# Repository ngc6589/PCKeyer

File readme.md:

# PCKeyer
## 概要

PCKeyer はお手持ちのエレキーと無線機の KEY ジャック間に入れることで、PCキーイング機能を追加するためのアダプタ基板です。

CTESTWIN や DSCW (Didital Sound CW) などから、シリアルポートの RTS/DTR を使用したキーイングをすることが出来ます。

パドル -> エレキー -> 当アダプタ -> リグのキージャック という接続です。

## プリント基板について

基板は https://www.em9system.com/?p=956 にて頒布いたします。

## 部品表  

|部品名|秋月型番|数量|その他|
|-----|-----|----|----|
|FT232RL USBシリアル変換モジュールキット|K-06693|1||
|抵抗入トランジスタ DTA123EL|I-12465|1||
|フォトカプラ PC817|I-13765|1||
|丸ピンICソケット(4P)|P-14240|1||
|カーボン抵抗(炭素皮膜抵抗) 1/4W180Ω(100本入)|R-25181|1袋||
|3.5mmステレオミニジャック MJ-352W-O|C-08958|2||
|ジャンパーピン赤(2.54mmピッチ)(25個入)|P-03688|1袋||
|ピンヘッダ 1×40 (40P)|C-00167|1||
|＜以下オプション＞
|C基板用アクリルパネル(アクリル板) 2mm厚(透明)|P-09853|1|スモークは P-09854|
|3mmプラネジ(7mm)+六角スペーサー(14mm)セット|P-01861|1||
|接着シール付き透明ゴムクッション (4個入)|P-10080|1||

抵抗入トランジスタ DTA123EL は、他のデジトラに置き換え可能です。または2SA1015 などの汎用 PNP トランジスタと 2.2k 程度のベース抵抗の組み合わせでも OK です。足の並びは ECB です。  
フォトカプラは TLP521 など汎用品置き換え可能です。  

## 組み立て

- FT232RL USBシリアル変換モジュールキットは、 USB からの 5V で動作させたいのでジャンパーJ1 2-3間ショート、J2 ショートとします。
- 0「ゼロ」と書かれた抵抗部分は、抵抗入りトランジスタを使用する場合はショートです。2SA1015 など汎用 PNP トランジスタを使うときだけここにベース抵抗を取り付けます。

## 注意事項

- 無線機の KEY 入力はストレートキーの設定にして下さい
- フォトカプラの耐圧から、真空管式リグのキーイングは出来ません。
- 本機を USB に差した時、 USB シリアルアダプタの初期化途中6回程送信状態になります。無線機が ON の状態だとその間送信状態となります。注意ください。

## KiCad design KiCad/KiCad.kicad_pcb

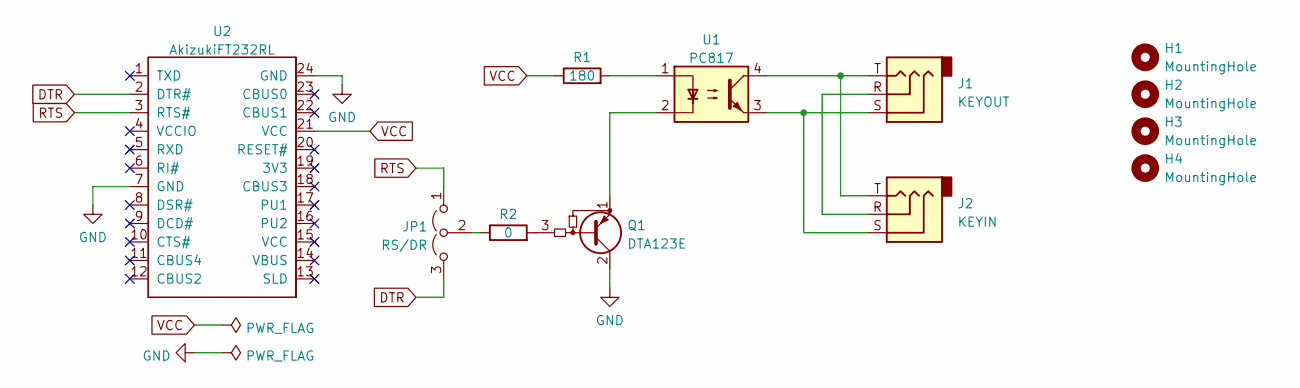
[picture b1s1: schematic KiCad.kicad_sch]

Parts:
H1, H2, H3, H4: MountingHole; MountingHole_3.2mm_M3
J1: KEYOUT; MJ-352W-0
J2: KEYIN; MJ-352W-0
JP1: RS/DR; PinHeader_1x03_P2.54mm_Vertical
Q1: DTA123E; TO-92_HandSolder
R1: 180; R_Axial_DIN0207_L6.3mm_D2.5mm_P7.62mm_Horizontal
R2: 0; R_Axial_DIN0207_L6.3mm_D2.5mm_P7.62mm_Horizontal
U1: PC817; DIP-4_W7.62mm_Socket_LongPads
U2: AkizukiFT232RL; DIP-24_W15.24mm_Socket_LongPads

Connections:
DTR: JP1.3 (B), U2.2 (DTR#)
GND: Q1.2 (C), U2.7 (GND), U2.24 (GND)
unnamed: J1.R, J2.R
unnamed: J1.S, J2.S, U1.3
unnamed: J1.T, J2.T, U1.4
unnamed: JP1.2 (C), R2.1
unnamed: Q1.1 (E), U1.2
unnamed: Q1.3 (B), R2.2
unnamed: R1.2, U1.1
RTS: JP1.1 (A), U2.3 (RTS#)
VCC: R1.1, U2.21 (VCC)

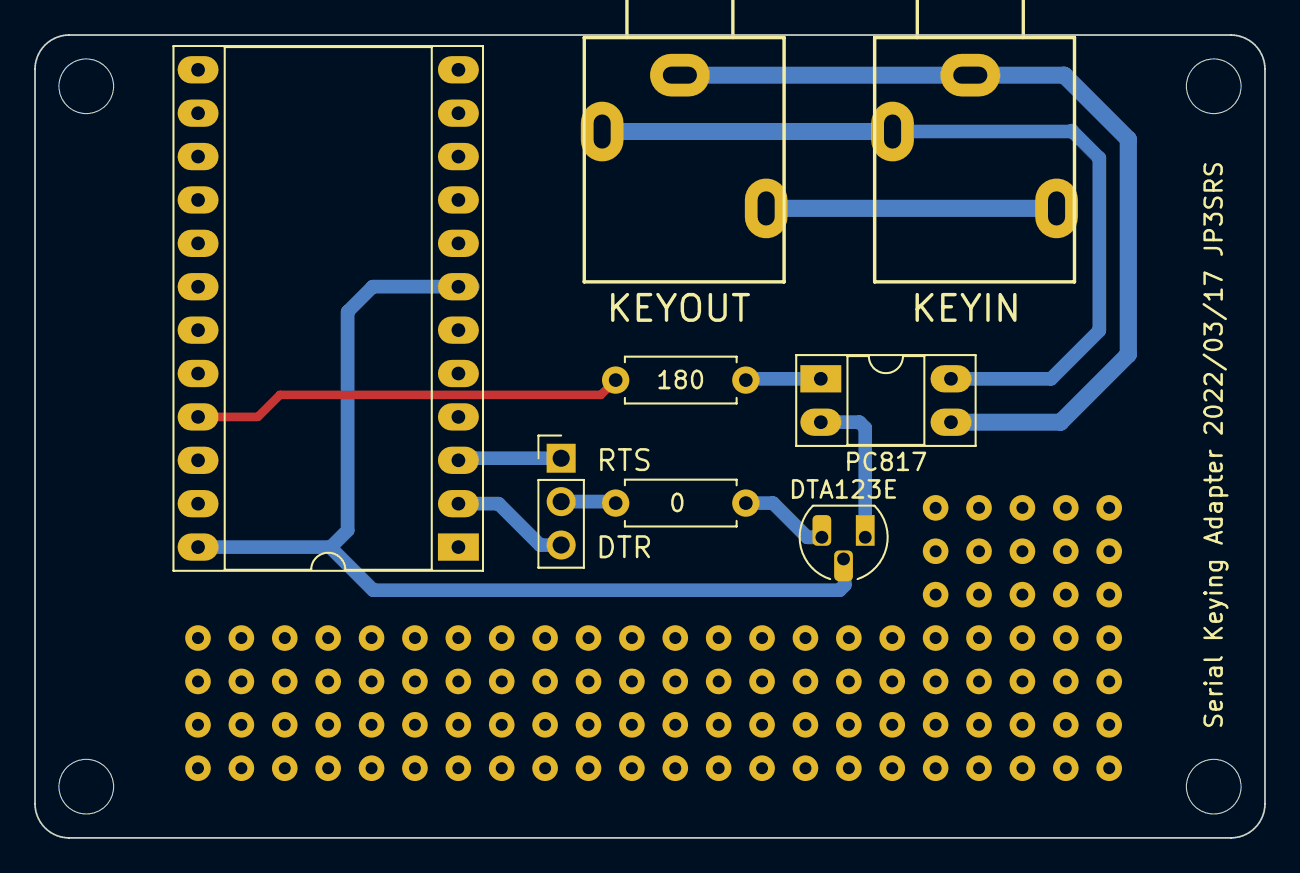
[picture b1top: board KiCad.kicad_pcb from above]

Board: 2 copper layers, 72.0 x 47.0 mm, 12 parts (0 on the bottom side), 11 nets.

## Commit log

2022-03-24 add photo
2022-04-20 Release zip file changed
